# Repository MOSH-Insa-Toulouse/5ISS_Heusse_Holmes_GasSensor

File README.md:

# M-OSH - Gas Sensor
Developed by Emily Holmes and Cyprien Heusse as part of the Microcontroller and Open Source Hardware course of Innovative Smart Systems.

## Project Aim
As part of the Innovative Smart Systems major, we worked on a gas sensor. For this project, our work started with the conception and creation of the sensor in the AIME laboratory. We then had to work on the schematics, the routing and wiring, programming, wireless communication and network aspects. 

This makes this project an excellent way of testing our abilities in multiple of the key expertise developed in this field: network knowledge, programming skills, electronics... 

In this report, we will describe all of the steps we undertook to obtain the final results. 

## GitHub Content

### Delivrables 

In this repository are the following files:
- On the main branch: 
    - LTSpice simulation files
    - KiCad schematics and routing files 
    - Arduino code for the smart sensor
    - Datasheet for the sensor
    - README.md
- On the FakeGasSensor branch: 
    - Arduino code to run a simpler version of the project, as described below, with a commercialized sensor. 

### Material required to run the project

To run the project, we used an Arduino UNO, a LoRa module, and the gas sensors conceived at the AIME laboratory. A more specific list of components is specified below. 

An access to a LoRa gateway and a network server (ChirpStack here) are also needed.

## Introduction to LoRa and Gas Sensors
To become more familiar with both gas sensors and the LoRa protocol, that we hadn't used up to that point, we decided to make a simple sample program. This sample program is available on the FakeGasSensor branch. 

### How to run the program
For this, we had to use the LoRa gateway at INSA via Chirpstack. To replicate this program, it is necessary to add the LoRa chip you use to the INSA network [here](https://srv-chirpstack.insa-toulouse.fr/). 

You will also need: 
- An Arduino UNO
- A RN2483 LoRa module and an antenna
- A MQ2 gas sensor (or a MQX sensor, but ensure you have gas you can test it with available. MQ2 is easy to test with a lighter)
- Cables 

### Troubleshooting
* If the LoRa module does not connect, ensure you have generated the right keys on Chirpstack. We use OTAA connection, so you need to run the program once to retrieve your chip's EUI.
* If the gas sensor does not seem to detect gas, you might need to adjust the potentiometer on the sensor, and/or alter the threshold value in the program.
* LoRa can be a bit slow. It is normal to wait a few seconds before receiving the message.

### Results
The program sends a message when gas is detected. This message is a "1" (which might read as "0x31" in ASCII). No more messages are sent until the gas level fall below the threshold and we send a "0" (which might read as "0x30" in ACSII).

Left: Gas sensor, top: RN2483 with antenna, bottom: Arduino UNO.

## AIME Gas Sensor and KiCad
After getting warmed up with the industrial sensor, we started working on the final project.

### Project Goals
As we want to create a smart sensor, it should be capable of performing various tasks without human intervention. Some of those tasks are:
- Calibrating itself
- Measuring its temperature and, if outside of operating temperature ranges, regenerate itself
- Recognizing a gas by comparing measured values to known characteristics
- Send data via LoRa to a gateway

### AIME Sensor
The sensor made at AIME has the following schematics:

There are 10 pins, which are:
- Two N.C. 
- The heating resistor (up to 20V).
- The temperature sensor.
- The gas sensors themselves (2 of them, so we could theorically have two areas for detecting and evene detect different gases).

## Amplifying the Signal from the Sensor
The gas sensor made has a huge resistance which varies depending on the presence of gas and on the nature of said gas. The value of the resistance will be around a G&Omega; meaning the current that will flow through it and to the ADC will be extremely small (around a nA). Since we will use an Arduino with only a 10-bit ADC, we need to amplify the signal exiting the gas sensor. To do so, we designed an amplifier circuit based on an operational amplifier using LTSpice. 

### LTSpice Simulation
The amplifier is based on 3 different filters, each with their own cutoff frequency. The first filter is centered around C1, R1 and R5, the second one from C4 and R3 and the last one from C2 and R4.
To better simulate the behaviour of the circuit, we created a component to simulate the gas sensor behavior as closely as possible. The sensor component is actually a circuit itself:

The circuit as a whole is as follows:

### Caracterizing the Amplification

Below are the cutoff frequencies of each filter.

| Filter | Cutoff frequency |
|--------|------------------|
| 1      | 16 Hz            |
| 2      | 1.6 Hz           |
| 3      | 1600 Hz          |

These filters have different purposes:
- The first filter is used to filter the sensor's noise itself
- The second filter is used to filter the 50Hz frequency from the power grid.
- The last filter is an anti-aliasing filter.

From this circuit we can deduce the resistance value of the gas sensor from the voltage on the ADC using the following formula:

Where R is the resistance of the sensor and V<sub>ADC</sub> is the voltage detected by the ADC (between 0 and +5V, coded between 0 and 1023).

## Printed Circuit Board (PCB) design using KiCad

As the PCB had to be printed following the university's requirements and technological limitations, we could only use one layer to route the circuit. 

The required components are: 
- 100nF capacitors (3)
- 1uF capacitor (1) 
- 100k&Omega; resistors (2)
- 10k&Omega; resistors (2)
- 1k&Omega; resistors (2)
- 100&Omega; resistor (1)
- LTC1050 pp-amp (1)
- MCP41100 potentiometer (1) 
- SLW12 two-position switch (1)
- Arduino Uno (1)
- IRF520 NMOS (1)
- 7-pin header (1) for a LoRa RN2483 module

And the gas sensor conceived at AIME in a TO-5 10-pin package. The PCB is made to work with an Arduino shield. 

Below is a view of the routed PCB on KiCad.

### Soldered PCB

The PCB, once soldered with the LoRa module and its antenna, is pictured below. As explained above, it is printed on the bottom layer. From top to bottom, you can see: the antenna (on the left, cutoff), the LoRa module, the PCB, and the Arduino shield.

## Programming the Sensor

The programming was done by creating functions for each of the states we defined above: regeneration, calibration, measuring, etc. The goal is for the system to be as autonomous as possible. 

To better get a grasp of the system, we conceived a finite state machine describing the various functions to be used. 

The core of the Arduino code is quite simple: 
- In the setup: 
    - We prepare the LoRa communication (initializeRadio)
    - We calibrate the gain via the potentiometer (calibration)
    - We let the user choose the operating temperature 
- In the core of the program: 
    - We check that the temperature is within the operating range (checkTemperature)
        - If not, we regenerate (regeneration) 
    - We measure the gas (measureGas) and send it (commLoRa)

### Gas Identification

As explained above, this sensor is capable to recognise between two different gases: Ethanol, and Ammonia. This is done by comparing the sensitibility regression curve of the measured gas (in Volts) to known values for both of these gases. 

### Improving Energy Consumption

Energy savings are one of the key metrics to keep track of in IoT. Here are some ways to improve the current systems to ensure low consumption: 
- Replacing the Arduino by a low-power microcontroller and programming at a lower level
- Optimizing the gas sensor so it does not require a 12V power supply
- Using a low energy protocol such as Bluetooth Low Energy, or conceiving a protocol for this specific application as we have done in other ISS courses.  

## Node-RED

To finalize this project, we created a dashboard using Node-RED to show the values sent via LoRa. 
A simple dashboard indicating the last message received along with the gas type, and the presence of gas. The flow is visible below, as well as a GIF of the dashboard in function.

## Conclusion and Future Work
By the end of the project, we have the core of a smart sensor system with the ability to monitor it on an external application. To finalize this work, it would be necessary to edit the program with accurate values for gas sensitivity from the sensor. 

Nevertheless, this repository provides a solid basis to conceive and use this smart sensor, with an approach from a physical, electronical, and software point of view.

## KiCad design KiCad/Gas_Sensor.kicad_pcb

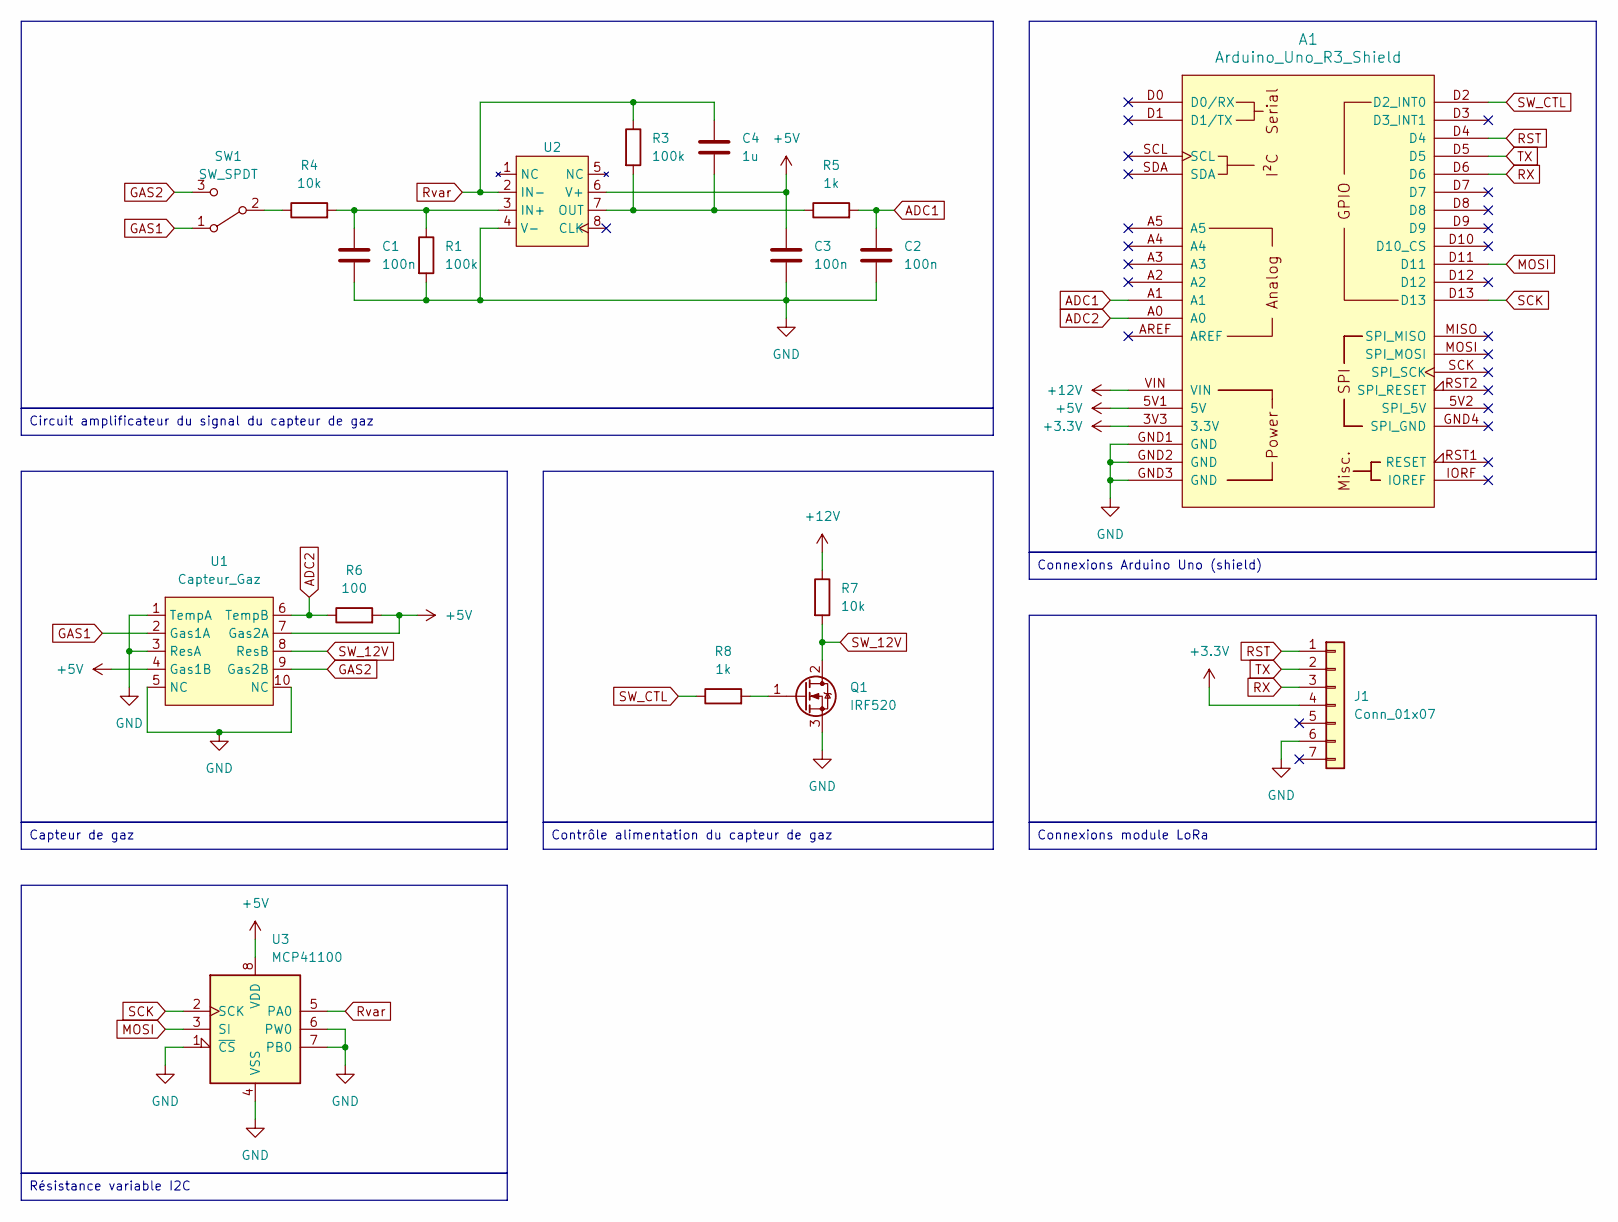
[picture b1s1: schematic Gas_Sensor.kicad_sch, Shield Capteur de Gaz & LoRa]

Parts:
A1: Arduino_Uno_R3_Shield
C1, C2, C3: 100n; C_Disc_D7.0mm_W2.5mm_P5.00mm
C4: 1u; C_Disc_D7.0mm_W2.5mm_P5.00mm
J1: Conn_01x07; PinHeader_1x07_P2.54mm_Vertical
Q1: IRF520; TO-220-3_Vertical
R1, R3: 100k; R_Axial_DIN0207_L6.3mm_D2.5mm_P10.16mm_Horizontal
R4, R7: 10k; R_Axial_DIN0207_L6.3mm_D2.5mm_P10.16mm_Horizontal
R5, R8: 1k; R_Axial_DIN0207_L6.3mm_D2.5mm_P10.16mm_Horizontal
R6: 100; R_Axial_DIN0207_L6.3mm_D2.5mm_P10.16mm_Horizontal
SW1: SW_SPDT; SLW12768644AD
U1: Capteur_Gaz; TO-5-10
U2: DIP-8_W7.62mm
U3: MCP41100; DIP-8_W7.62mm

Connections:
+3.3V: A1.3V3 (3.3V), J1.4
+5V: A1.5V1 (5V), C3.1, R6.2, U1.4 (Gas1B), U1.7 (Gas2A), U2.6 (V+), U3.8 (VDD)
+12V: A1.VIN, R7.1
ADC1: A1.A1, C2.1, R5.2
ADC2: A1.A0, R6.1, U1.6 (TempB)
GAS1: SW1.1 (A), U1.2 (Gas1A)
GAS2: SW1.3 (C), U1.9 (Gas2B)
GND: A1.GND1 (GND), A1.GND2 (GND), A1.GND3 (GND), C1.2, C2.2, C3.2, J1.6, Q1.3 (S), R1.2, U1.1 (TempA), U1.3 (ResA), U1.5 (NC), U1.10 (NC), U2.4 (V-), U3.1 (~CS), U3.4 (VSS), U3.6 (PW0), U3.7 (PB0)
MOSI: A1.D11, U3.3 (SI)
unnamed: Q1.1 (G), R8.2
unnamed: R4.1, SW1.2 (B)
unnamed: C1.1, R1.1, R4.2, U2.3 (IN+)
unnamed: C4.2, R3.2, R5.1, U2.7 (OUT)
RST: A1.D4, J1.1
RX: A1.D6, J1.3
Rvar: C4.1, R3.1, U2.2 (IN-), U3.5 (PA0)
SCK: A1.D13, U3.2 (SCK)
SW_12V: Q1.2 (D), R7.2, U1.8 (ResB)
SW_CTL: A1.D2 (D2_INT0), R8.1
TX: A1.D5, J1.2

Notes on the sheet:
Capteur de gaz
Connexions module LoRa
Connexions Arduino Uno (shield)
Circuit amplificateur du signal du capteur de gaz
Résistance variable I2C
Contrôle alimentation du capteur de gaz

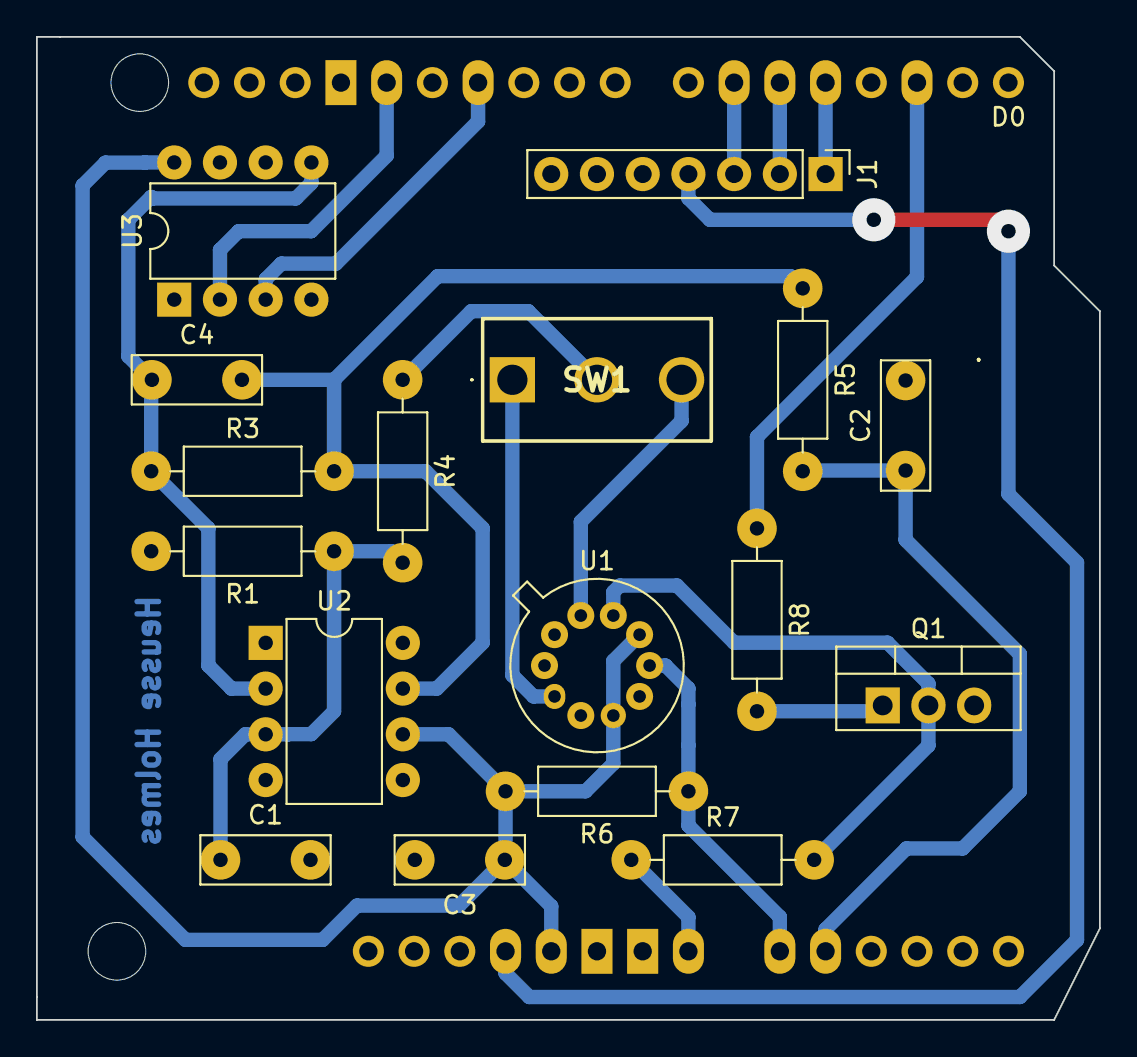
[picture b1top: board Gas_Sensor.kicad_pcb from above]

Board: 2 copper layers, 59.1 x 54.6 mm, 18 parts (0 on the bottom side), 20 nets.

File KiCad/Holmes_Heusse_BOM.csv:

"Source:","/Users/cyprienh/Documents/1 - INSA/5A/Sensors/Gas_Sensor/Gas_Sensor.kicad_sch"
"Date:","Wednesday, December 13, 2023 at 08:09:01 AM"
"Tool:","Eeschema 7.0.9"
"Generator:","/Applications/KiCad/KiCad.app/Contents/SharedSupport/plugins/bom_csv_grouped_by_value.py"
"Component Count:","18"

"Collated Components:"

"Item","Qty","Reference(s)","Value","LibPart","Footprint","Datasheet","DNP"
"1","1","A1","Arduino_Uno_R3_Shield","PCM_arduino-library:Arduino_Uno_R3_Shield","PCM_arduino-library:Arduino_Uno_R3_Shield","https://docs.arduino.cc/hardware/uno-rev3",""
"2","3","C1, C2, C3","100n","Device:C","Capacitor_THT:C_Disc_D7.0mm_W2.5mm_P5.00mm","~",""
"3","1","C4","1u","Device:C","Capacitor_THT:C_Disc_D7.0mm_W2.5mm_P5.00mm","~",""
"4","1","J1","Conn_01x07","Connector_Generic:Conn_01x07","Connector_PinHeader_2.54mm:PinHeader_1x07_P2.54mm_Vertical","~",""
"5","1","Q1","IRF520","Transistor_FET:IRF540N","Package_TO_SOT_THT:TO-220-3_Vertical","http://www.irf.com/product-info/datasheets/data/irf540n.pdf",""
"6","2","R1, R3","100k","Device:R","Resistor_THT:R_Axial_DIN0207_L6.3mm_D2.5mm_P10.16mm_Horizontal","~",""
"7","2","R4, R7","10k","Device:R","Resistor_THT:R_Axial_DIN0207_L6.3mm_D2.5mm_P10.16mm_Horizontal","~",""
"8","2","R5, R8","1k","Device:R","Resistor_THT:R_Axial_DIN0207_L6.3mm_D2.5mm_P10.16mm_Horizontal","~",""
"9","1","R6","100","Device:R","Resistor_THT:R_Axial_DIN0207_L6.3mm_D2.5mm_P10.16mm_Horizontal","~",""
"10","1","SW1","SW_SPDT","Switch:SW_SPDT","Gas:SLW12768644AD","~",""
"11","1","U1","Capteur_Gaz","Gas:gas_sensor","Package_TO_SOT_THT:TO-5-10","",""
"12","1","U2","~","Gas:LTC1050","Package_DIP:DIP-8_W7.62mm","",""
"13","1","U3","MCP41100","Potentiometer_Digital:MCP41100","Package_DIP:DIP-8_W7.62mm","http://ww1.microchip.com/downloads/en/DeviceDoc/11195c.pdf",""

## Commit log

2023-12-01 Arduino code for MQ2 sensor
2023-12-05 Add readme for first part
2023-12-05 Add readme to master
2023-12-13 Added KiCad files for the shield's PCB
2023-12-19 code for smart sensor
2023-12-19 README update
2023-12-19 Added LTSpice files
2023-12-21 nodered readme
2023-12-29 add nodered dashboard
2024-01-22 Added datasheet
